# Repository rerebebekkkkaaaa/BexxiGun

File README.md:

arduino ide: 
-board:"ESP32 Dev Module" oder "AI Thinker ESP32-CAM"
-Port(linux):"/dev/ttyUSB0"

flashen:
1.flash pin einstecken
2.power aus
3.power an
4.upload
5.flash pin aus
6.power aus
7.power an 

LIBS:
FastLed = 3.9.7
https://github.com/me-no-dev/ESPAsyncWebServer = 3.4.0
 https://github.com/ayushsharma82/ElegantOTA = 3.1.6
ArduinoJson(https://arduinojson.org/) =7.2.1

Partition Scheme (for OTA!!!!):
Minimal SPIFFSS

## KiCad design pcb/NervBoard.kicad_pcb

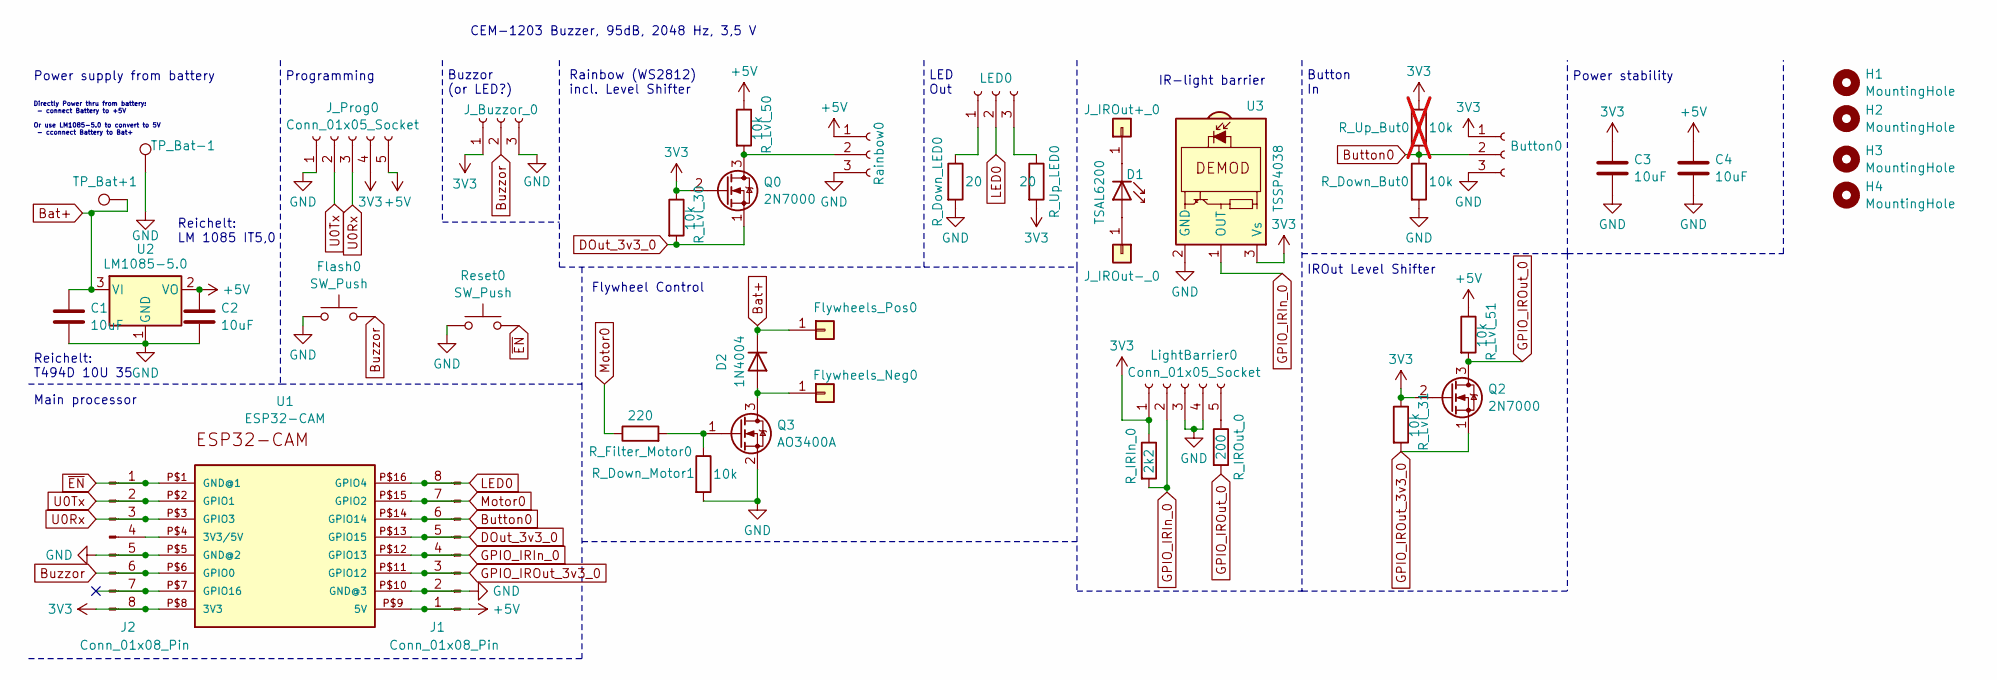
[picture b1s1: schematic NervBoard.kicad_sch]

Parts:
Button0: Conn_01x03_Socket; PinSocket_1x03_P2.54mm_Vertical; MPN BG302-03-A-L-G
C1, C2, C3, C4: 10uF; CP_EIA-6032-15_Kemet-U_Pad2.25x2.35mm_HandSolder; MPN T491U106K020AT
D1: TSAL6200; MPN TSAL6200
D2: 1N4004; D_DO-41_SOD81_P10.16mm_Horizontal; MPN 1N4004-B
Flash0: SW_Push; SW_PUSH_6mm_H4.3mm; MPN TS02-66-43-BK-160-SCR-D
Flywheels_Neg0: Conn_01x01; TestPoint_THTPad_3.0x3.0mm_Drill1.5mm
Flywheels_Pos0: Conn_01x01; TestPoint_THTPad_D3.0mm_Drill1.5mm
H1: MountingHole; MountingHole_3.2mm_M3
H2, H3, H4: MountingHole; MountingHole__Langloch_3.2mm_M3
J1, J2: Conn_01x08_Pin; PinSocket_1x08_P2.54mm_Vertical; MPN SL-108-TT-11
J_Buzzor_0: Conn_01x03_Socket; PinSocket_1x03_P2.54mm_Horizontal_NoPrint; MPN BG302-03-A-L-G
J_IROut+_0: (no value)
J_IROut-_0: (no value)
J_Prog0: Conn_01x05_Socket; PinSocket_1x05_P2.54mm_Horizontal_NoPrint; MPN BG302-05-A-L-G
LED0: Conn_01x03_Socket; PinSocket_1x03_P2.54mm_Vertical; MPN BG302-03-A-L-G
LightBarrier0: Conn_01x05_Socket; PinSocket_1x05_P2.54mm_Horizontal_NoPrint; MPN BG302-05-A-L-G
Q0, Q2: 2N7000; TO-92_Inline; MPN 2N7000TA
Q3: AO3400A; SOT-23; MPN AO3400A
R_Down_But0: 10k; R_0805_2012Metric_Pad1.20x1.40mm_HandSolder; MPN RT0805FRE0710KL
R_Down_LED0: 20; R_0805_2012Metric_Pad1.20x1.40mm_HandSolder; MPN RT0805FRE0720RL
R_Down_Motor1: 10k; R_0805_2012Metric_Pad1.20x1.40mm_HandSolder; MPN RT0805FRE0710KL
R_Filter_Motor0: 220; R_0805_2012Metric_Pad1.20x1.40mm_HandSolder; MPN RT0805FRE07220RL
R_IRIn_0: 2k2; R_0805_2012Metric_Pad1.20x1.40mm_HandSolder; MPN RT0805FRE072K2L
R_IROut_0: 200; R_0805_2012Metric_Pad1.20x1.40mm_HandSolder; MPN RT0805FRE07200RL
R_Lvl_30, R_Lvl_31, R_Lvl_50, R_Lvl_51: 10k; R_0805_2012Metric_Pad1.20x1.40mm_HandSolder; MPN RT0805FRE0710KL
R_Up_But0: 10k; R_0805_2012Metric_Pad1.20x1.40mm_HandSolder; MPN RT0805FRE0710KL; not fitted
R_Up_LED0: 20; R_0805_2012Metric_Pad1.20x1.40mm_HandSolder; MPN RT0805FRE0720RL
Rainbow0: Conn_01x03_Socket; PinSocket_1x03_P2.54mm_Horizontal_NoPrint; MPN BG302-03-A-L-G
Reset0: SW_Push; SW_PUSH_6mm_H4.3mm; MPN TS02-66-43-BK-160-SCR-D
TP_Bat+1: TestPoint; TestPoint_THTPad_D3.0mm_Drill1.5mm
TP_Bat-1: TestPoint; TestPoint_THTPad_3.0x3.0mm_Drill1.5mm
U1: ESP32-CAM; MPN ESP32-CAM
U2: LM1085-5.0; TO-220-3_Horizontal_TabDown; MPN LM1085IT-5.0/NOPB
U3: TSSP4038; MPN TSSP4038

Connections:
3V3: Button0.1, C3.1, J2.8, J_Buzzor_0.1, J_Prog0.4, LightBarrier0.1, Q0.2 (G), Q2.2 (G), R_IRIn_0.1, R_Lvl_30.1, R_Lvl_31.1, R_Up_But0.1, R_Up_LED0.2, U1.P$8 (3V3), U3.3 (Vs)
+5V: C2.1, C4.1, J1.1, J_Prog0.5, R_Lvl_50.1, R_Lvl_51.1, Rainbow0.1, U1.P$9 (5V), U2.2 (VO)
Bat+: C1.1, D2.1 (K), Flywheels_Pos0.1, TP_Bat+1.1, U2.3 (VI)
Button0: Button0.2, J1.6, R_Down_But0.1, R_Up_But0.2, U1.P$14 (GPIO14)
Buzzor: Flash0.2, J2.6, J_Buzzor_0.2, U1.P$6 (GPIO0)
DOut_3v3_0: J1.5, Q0.1 (S), R_Lvl_30.2, U1.P$13 (GPIO15)
GND: Button0.3, C1.2, C2.2, C3.2, C4.2, Flash0.1, J1.2, J2.5, J_Buzzor_0.3, J_Prog0.1, LightBarrier0.3, LightBarrier0.4, Q3.2 (S), R_Down_But0.2, R_Down_LED0.2, R_Down_Motor1.2, Rainbow0.3, Reset0.1, TP_Bat-1.1, U1.P$5 (GND@2), U1.P$10 (GND@3), U2.1 (GND), U3.2 (GND)
GPIO_IRIn_0: J1.4, LightBarrier0.2, R_IRIn_0.2, U1.P$12 (GPIO13), U3.1 (OUT)
GPIO_IROut_0: Q2.3 (D), R_IROut_0.2, R_Lvl_51.2
GPIO_IROut_3v3_0: J1.3, Q2.1 (S), R_Lvl_31.2, U1.P$11 (GPIO12)
LED0: J1.8, LED0.2, U1.P$16 (GPIO4)
Motor0: J1.7, R_Filter_Motor0.1, U1.P$15 (GPIO2)
unnamed: D1.1 (K), J_IROut+_0.1
unnamed: D1.2 (A), J_IROut-_0.1
unnamed: D2.2 (A), Flywheels_Neg0.1, Q3.3 (D)
unnamed: J2.4, U1.P$4 (3V3/5V)
unnamed: LED0.1, R_Down_LED0.1
unnamed: LED0.3, R_Up_LED0.1
unnamed: LightBarrier0.5, R_IROut_0.1
unnamed: Q0.3 (D), R_Lvl_50.2, Rainbow0.2
unnamed: Q3.1 (G), R_Down_Motor1.1, R_Filter_Motor0.2
U0Rx: J2.3, J_Prog0.3, U1.P$3 (GPIO3)
U0Tx: J2.2, J_Prog0.2, U1.P$2 (GPIO1)
~EN: J2.1, Reset0.2, U1.P$1 (GND@1)

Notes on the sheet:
Reichelt: T494D 10U 35
Flywheel Control
Programming
Main processor
Button In
LED Out
Power stability
IROut Level Shifter
Power supply from battery
Directly Power thru from battery: - connect Battery to +5V Or use LM1085-5.0 to convert to 5V - cconnect Battery to Bat+
Reichelt: LM 1085 IT5,0
CEM-1203 Buzzer, 95dB, 2048 Hz, 3,5 V
Buzzor (or LED?)
Rainbow (WS2812) incl. Level Shifter
IR-light barrier

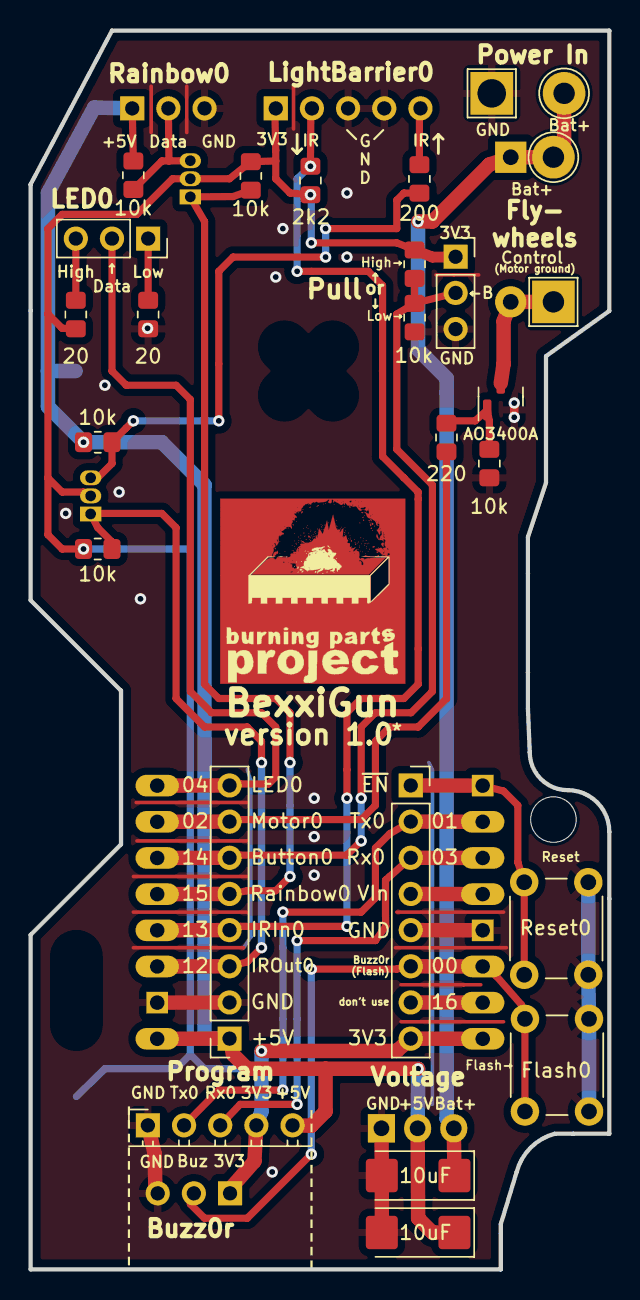
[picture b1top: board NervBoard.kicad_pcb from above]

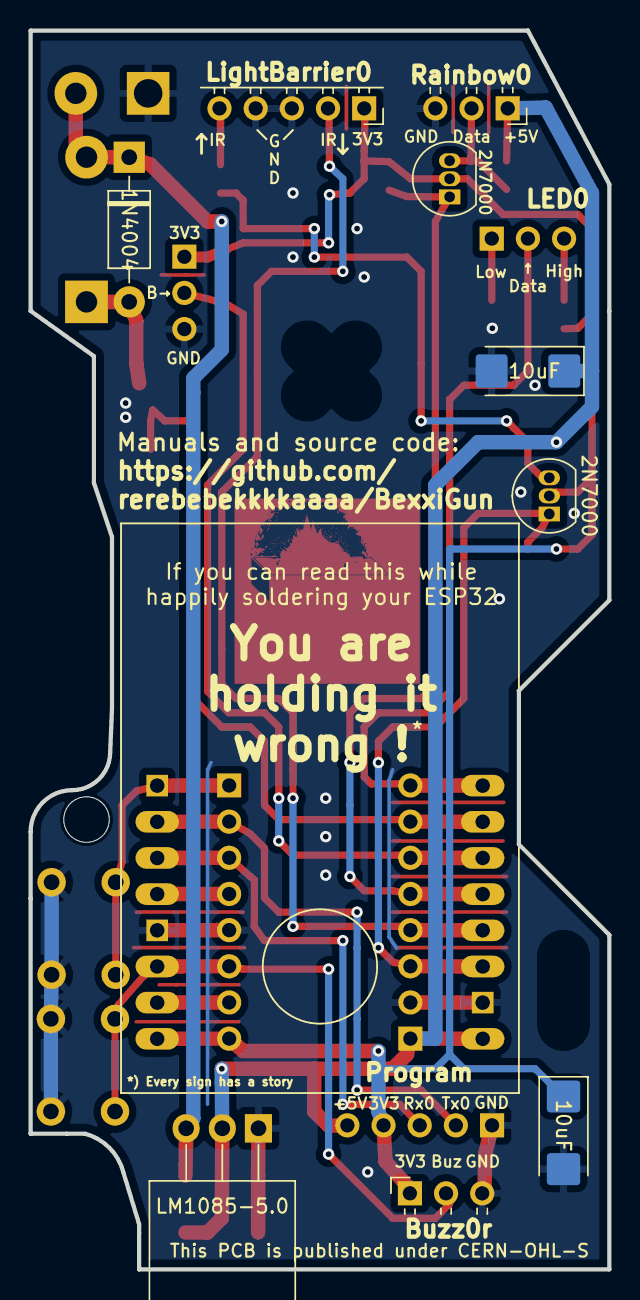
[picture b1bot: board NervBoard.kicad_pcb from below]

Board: 2 copper layers, 40.6 x 87.0 mm, 40 parts (10 on the bottom side), 22 nets.

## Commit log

2023-12-29 Not working interrupt initial state
2023-12-29 Working version flywheel button
2023-12-29 not working flywheel power up stuff
2023-12-29 Moved button pull and motor control into tasks
2023-12-30 I fixed the code someone else messed upgit add *111git add *elfgit add *
2023-12-30 pew pew pew pew no bling yet
2023-12-30 bling bling pew pew working
2023-12-30 pew pew bling bling 37c3 final sw load
2023-12-31 clean code und so refactoring kram
2024-01-02 Added a new pcb version. Fixed some flawes from v0.1, moved GPIOs, stailized power supply, added additional level shifters
2024-01-03 zwischenstand
2024-01-05 Added improved version of pcb v0.2 with full rewiring, focus on a more stable ground and broader wires.
2024-01-06 added Webserver and OTAupdates
2024-01-07 improved webpage and request handling
2024-01-09 working sw for lunchtime seminar
2024-01-11 Improved board to a stable version
2024-01-11 Added a LICENSE to make PCB re-usable
2024-01-12 updated .gitignore
2024-01-12 added secret wifi credentials (includes IR test code)
2024-01-31 Added support (very lazy, indeed) for lightbarrier/bolt detection
2024-02-03 working lightbarrier but unstable dart-speed measurement
2024-03-17 Working lightbarrier and dart speed measurement
2024-12-27 Tv b Gone first draft

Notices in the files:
pcb/NervBoard.kicad_pcb:
This PCB is published under CERN-OHL-S
